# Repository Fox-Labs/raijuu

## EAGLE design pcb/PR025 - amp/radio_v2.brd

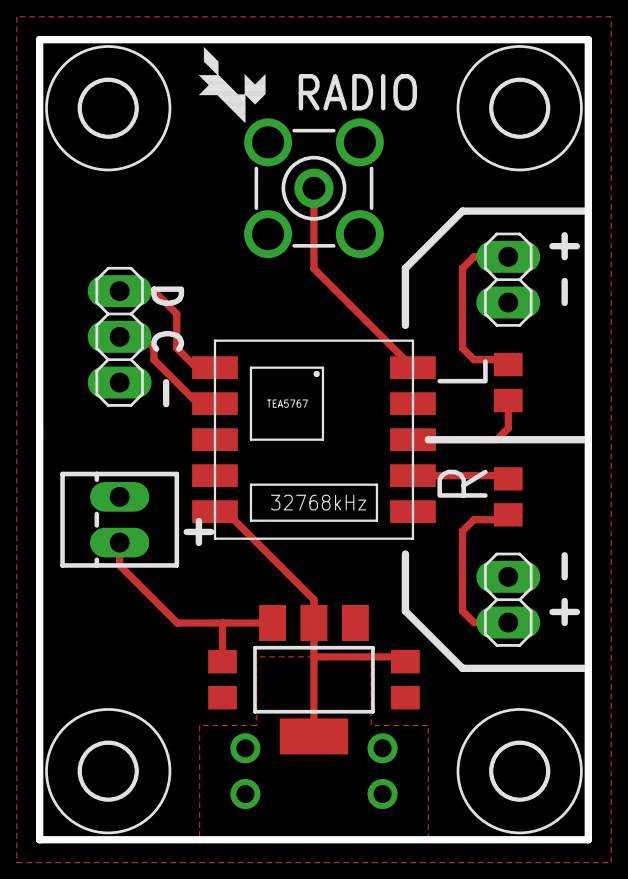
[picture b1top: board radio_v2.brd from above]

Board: 2 copper layers, 30.5 x 44.5 mm, 16 parts (0 on the bottom side), 10 nets.

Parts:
C1, C4: 10uF; C0805K
C2, C3: 1uF; C0805K
IC1: LM1117S; SOT223
JP1: 1X03
JP2: OUT_L; 1X02
JP3: OUT_R; 1X02
U1: TEA5767
U$1, U$2, U$3, U$4: 3,0
U$5: FOX-1
X1: 22-23-2021
X2: BU-SMA-V

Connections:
+3V3: C4.1, IC1.2, IC1.4, U1.5
GND: C1.2, C4.2, IC1.1, JP1.3, JP2.2, JP3.2, U1.3, U1.6, X1.2, X2.2, X2.3, X2.4, X2.5
unnamed: U1.10, X2.1
unnamed: C3.1, U1.7
unnamed: C3.2, JP3.1
unnamed: C2.2, JP2.1
OUT_R: C2.1, U1.8
SCL: JP1.2, U1.2
SDA: JP1.1, U1.1
VCC: C1.1, IC1.3, X1.1

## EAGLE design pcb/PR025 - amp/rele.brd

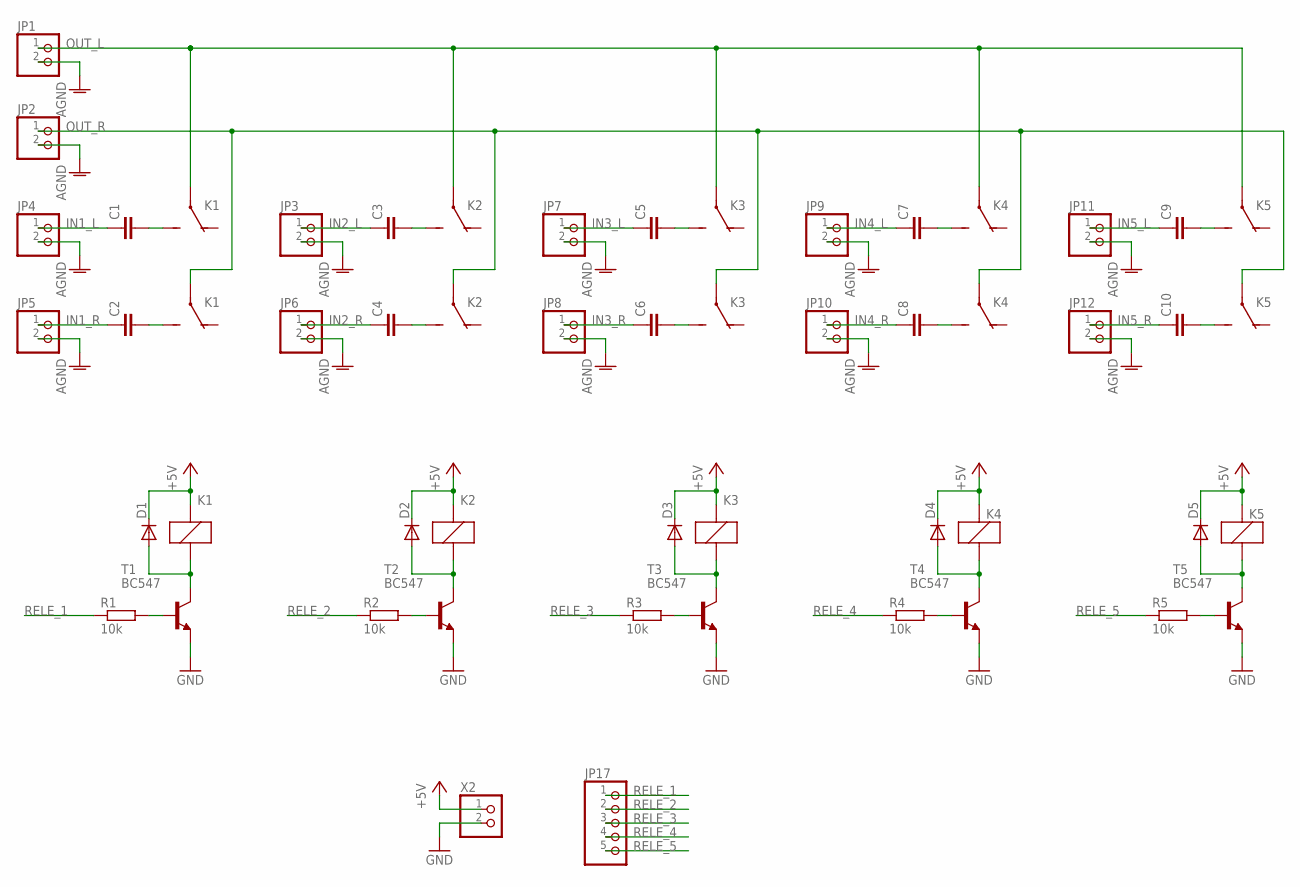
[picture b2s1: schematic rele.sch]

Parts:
C1, C2, C3, C4, C5, C6, C7, C8, C9, C10: C-EU050-025X075; C050-025X075
D1, D2, D3, D4, D5: 1N4004A; DO41-5
JP1, JP2, JP3, JP4, JP5, JP6, JP7, JP8, JP9, JP10, JP11, JP12: PINHD-1X2; 1X02
JP17: PINHD-1X5; 1X05
K1, K2, K3, K4, K5: MICRO-RELAY
R1, R2, R3, R4, R5: 10k; 0207/7
T1, T2, T3, T4, T5: BC547; TO92-
X2: 22-23-2021

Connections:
+5V: D1.C, D2.C, D3.C, D4.C, D5.C, K1.A1 (1), K2.A1 (1), K3.A1 (1), K4.A1 (1), K5.A1 (1), X2.1
AGND: JP1.2, JP2.2, JP3.2, JP4.2, JP5.2, JP6.2, JP7.2, JP8.2, JP9.2, JP10.2, JP11.2, JP12.2
GND: T1.1 (E), T2.1 (E), T3.1 (E), T4.1 (E), T5.1 (E), X2.2
IN1_L: C1.1, JP4.1
IN1_R: C2.1, JP5.1
IN2_L: C3.1, JP3.1
IN2_R: C4.1, JP6.1
IN3_L: C5.1, JP7.1
IN3_R: C6.1, JP8.1
IN4_L: C7.1, JP9.1
IN4_R: C8.1, JP10.1
IN5_L: C9.1, JP11.1
IN5_R: C10.1, JP12.1
unnamed: C2.2, K1.24 (S)
unnamed: C1.2, K1.14 (S)
unnamed: D1.A, K1.A2 (2), T1.2 (C)
unnamed: R1.2, T1.3 (B)
unnamed: C3.2, K2.14 (S)
unnamed: C4.2, K2.24 (S)
unnamed: C6.2, K3.24 (S)
unnamed: C5.2, K3.14 (S)
unnamed: C8.2, K4.24 (S)
unnamed: C7.2, K4.14 (S)
unnamed: D2.A, K2.A2 (2), T2.2 (C)
unnamed: D3.A, K3.A2 (2), T3.2 (C)
unnamed: D4.A, K4.A2 (2), T4.2 (C)
unnamed: R2.2, T2.3 (B)
unnamed: R3.2, T3.3 (B)
unnamed: R4.2, T4.3 (B)
unnamed: C10.2, K5.24 (S)
unnamed: C9.2, K5.14 (S)
unnamed: D5.A, K5.A2 (2), T5.2 (C)
unnamed: R5.2, T5.3 (B)
OUT_L: JP1.1, K1.11, K2.11, K3.11, K4.11, K5.11
OUT_R: JP2.1, K1.21, K2.21, K3.21, K4.21, K5.21
RELE_1: JP17.1, R1.1
RELE_2: JP17.2, R2.1
RELE_3: JP17.3, R3.1
RELE_4: JP17.4, R4.1
RELE_5: JP17.5, R5.1

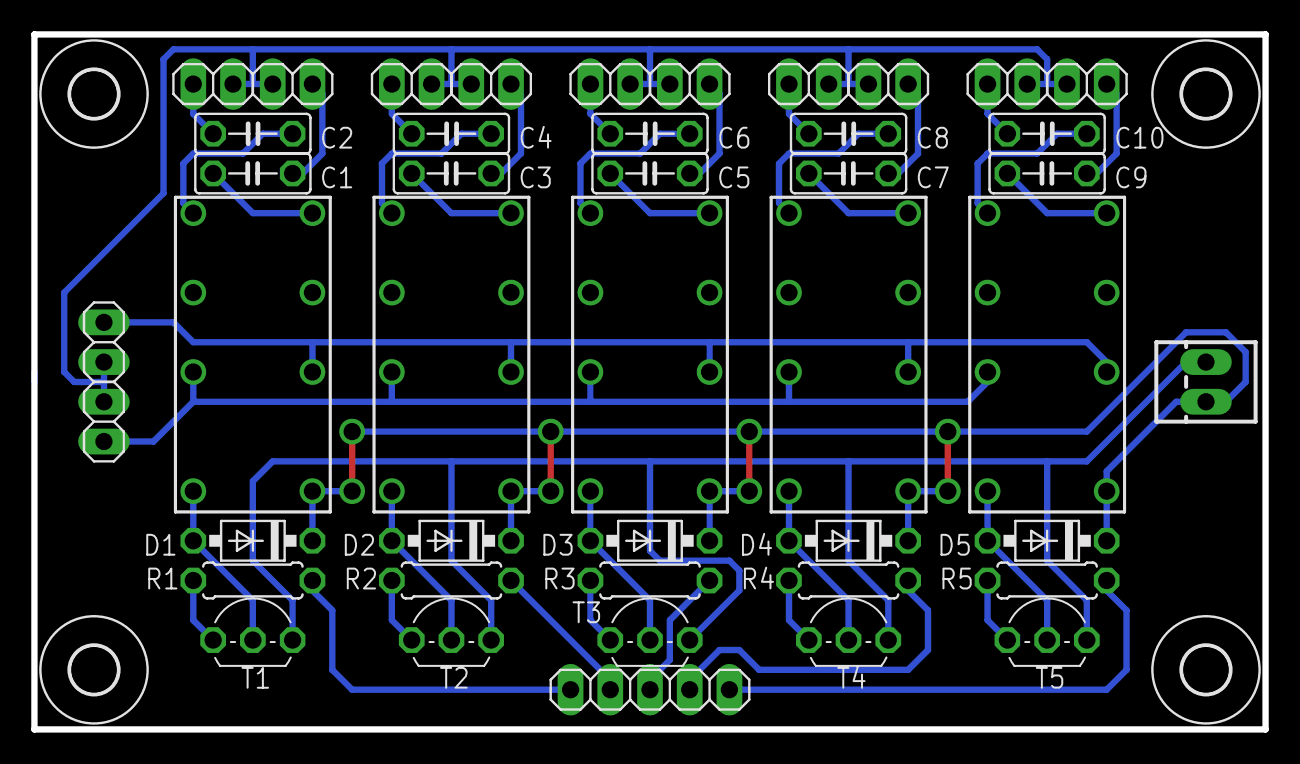
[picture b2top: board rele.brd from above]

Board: 2 copper layers, 78.7 x 44.5 mm, 48 parts (0 on the bottom side), 40 nets.

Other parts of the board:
U$1, U$2, U$3, U$4: 3,0

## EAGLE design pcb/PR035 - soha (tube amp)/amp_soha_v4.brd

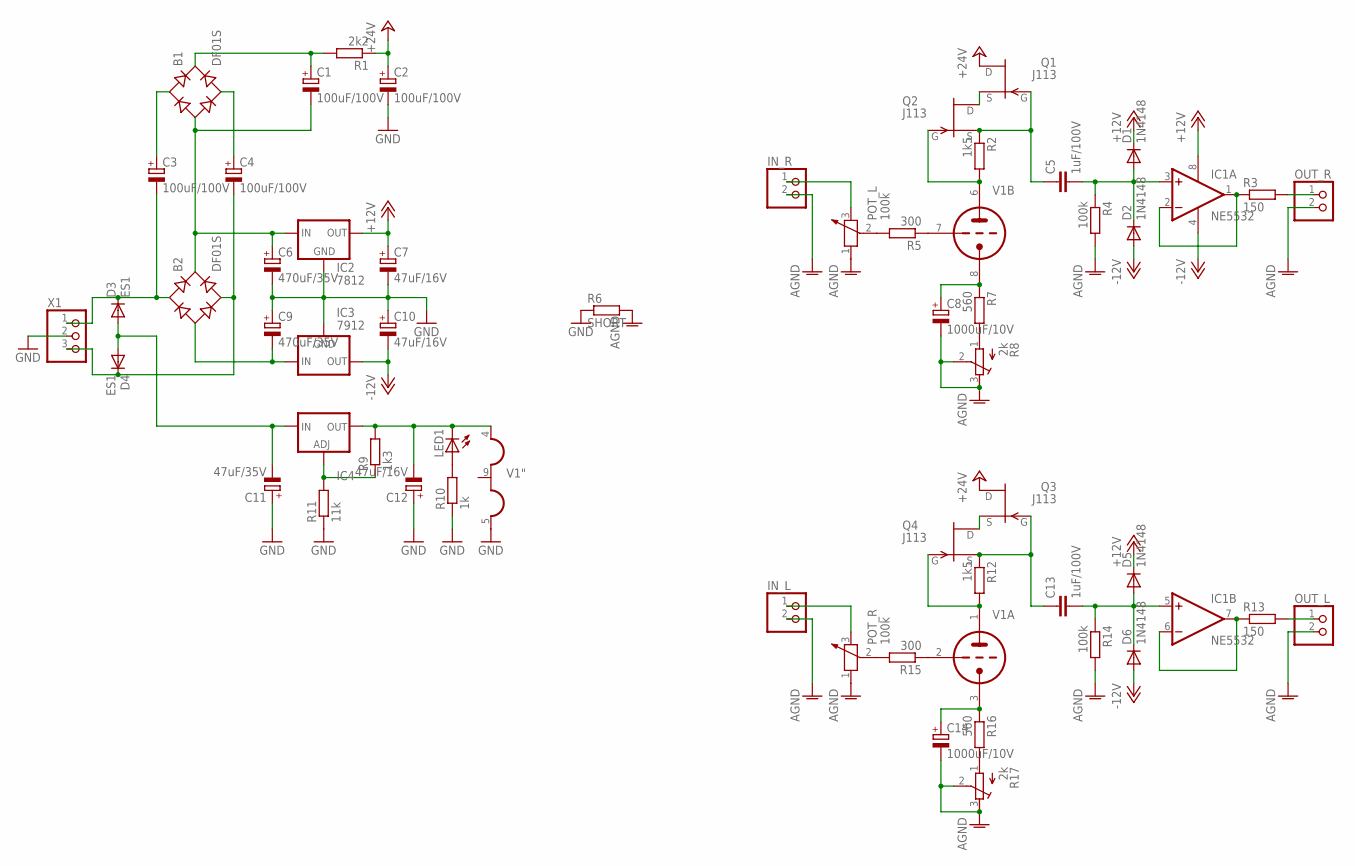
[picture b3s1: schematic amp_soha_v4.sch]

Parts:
B1, B2: DF01S; DFS
C1, C2, C3, C4: 100uF/100V; E5-10,5
C5, C13: 1uF/100V; C075-052X106
C6, C9: 470uF/35V; E5-10,5
C7, C10, C12: 47uF/16V; E2,5-6
C8, C14: 1000uF/10V; E5-10,5
C11: 47uF/35V; E2,5-6
D1, D2, D5, D6: 1N4148; D0805
D3, D4: ES1; DO-214AC
IC1: NE5532; SO08
IC2: 7812; 78XXS
IC3: 7912; 79XXS
IC4: LM337TS; 337TS
IN_L: PINHD-1X2; 1X02
IN_R: PINHD-1X2; 1X02
LED1: LED5MM
OUT_L: PINHD-1X2; 1X02
OUT_R: PINHD-1X2; 1X02
POT_L: 100k; 1X03
POT_R: 100k; 1X03
Q1, Q2, Q3, Q4: J113; TO92
R1: 2k2; R0805
R2, R12: 1k5; R0805
R3, R13: 150; R0805
R4, R14: 100k; R0805
R5, R15: 300; R0805
R6: SHORT
R7, R16: 560; R0805
R8, R17: 2k; RTRIM3296W
R9: 1k3; R0805
R10: 1k; R0805
R11: 11k; R0805
V1: 12AU7-P; NOVAL
X1: W237-103

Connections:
+12V: C7.+, D1.K (C), D5.K (C), IC1.8 (V+), IC2.OUT
+24V: C2.+, Q1.3 (D), Q3.3 (D), R1.1
-12.6V: C12.-, IC4.3 (OUT), LED1.K (C), R9.2, V1.4 (H1)
-12V: C10.-, D2.A, D6.A, IC1.4 (V-), IC3.OUT
AGND: C8.-, C14.-, IN_L.2, IN_R.2, OUT_L.2, OUT_R.2, POT_L.1, POT_R.1, R4.2, R6.2, R8.2 (S), R8.3 (E), R14.2, R17.2 (S), R17.3 (E)
GND: C2.-, C6.-, C7.-, C9.+, C10.+, C11.+, C12.+, IC2.GND, IC3.GND, R6.1, R10.1, R11.1, V1.5 (H3), X1.2
unnamed: B2.AC1, C3.-, D3.C, X1.1
unnamed: B2.AC2, C4.-, D4.C, X1.3
unnamed: C11.-, D3.A, D4.A, IC4.2 (IN)
unnamed: IC4.1 (ADJ), R9.1, R11.2
unnamed: B2.-, C9.-, IC3.IN
unnamed: B1.-, B2.+, C1.-, C6.+, IC2.IN
unnamed: LED1.A, R10.2
unnamed: B1.AC1, C3.+
unnamed: B1.AC2, C4.+
unnamed: R15.1, V1.2 (TG)
unnamed: B1.+, C1.+, R1.2
unnamed: IN_R.1, POT_L.3 (2)
unnamed: POT_L.2 (3), R5.2
unnamed: R5.1, V1.7 (TG)
unnamed: C8.+, R7.1, V1.8 (TK)
unnamed: C5.1, Q1.1 (G), Q2.2 (S), R2.1
unnamed: R7.2, R8.1 (A)
unnamed: R16.2, R17.1 (A)
unnamed: Q2.1 (G), R2.2, V1.6 (TA)
unnamed: Q1.2 (S), Q2.3 (D)
unnamed: Q4.1 (G), R12.2, V1.1 (TA)
unnamed: C5.2, D1.A, D2.K (C), IC1.3 (+IN), R4.1
unnamed: IC1.1 (OUT), IC1.2 (-IN), R3.1
unnamed: OUT_R.1, R3.2
unnamed: IN_L.1, POT_R.3 (2)
unnamed: POT_R.2 (3), R15.2
unnamed: C14.+, R16.1, V1.3 (TK)
unnamed: C13.1, Q3.1 (G), Q4.2 (S), R12.1
unnamed: Q3.2 (S), Q4.3 (D)
unnamed: C13.2, D5.A, D6.K (C), IC1.5 (+IN), R14.1
unnamed: IC1.6 (-IN), IC1.7 (OUT), R13.1
unnamed: OUT_L.1, R13.2

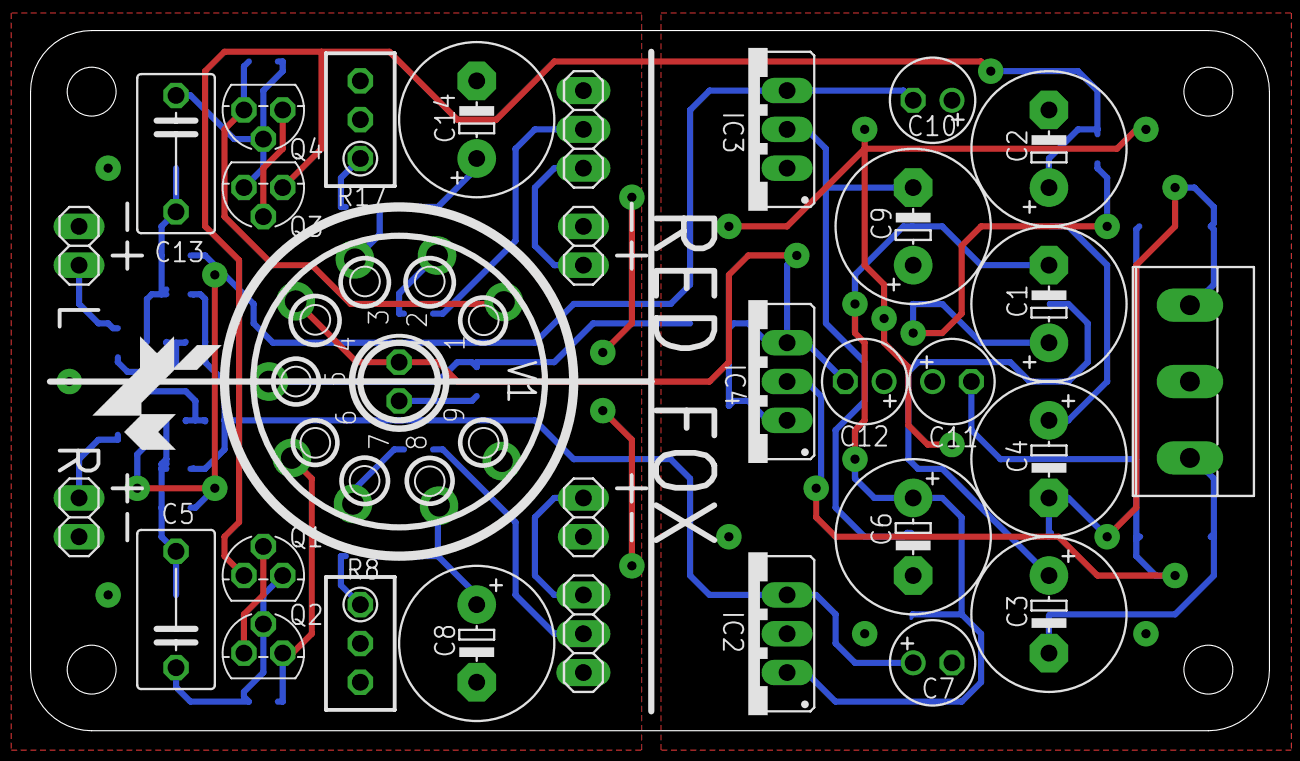
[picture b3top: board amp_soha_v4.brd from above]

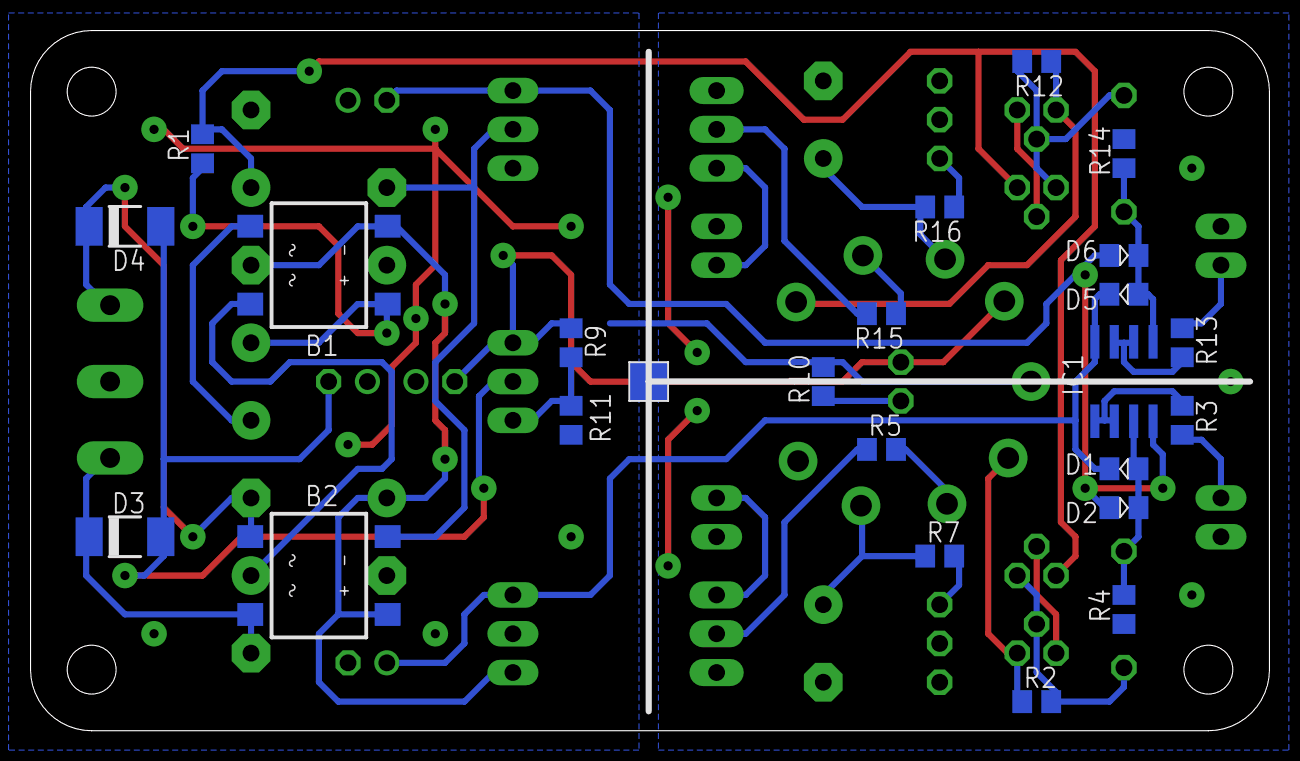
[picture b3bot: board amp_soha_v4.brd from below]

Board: 2 copper layers, 81.1 x 45.8 mm, 57 parts (24 on the bottom side), 38 nets.

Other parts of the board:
U$1: FOX-2
